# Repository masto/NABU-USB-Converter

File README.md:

# NABU-USB-Converter

Adapter to use a USB keyboard with the NABU PC

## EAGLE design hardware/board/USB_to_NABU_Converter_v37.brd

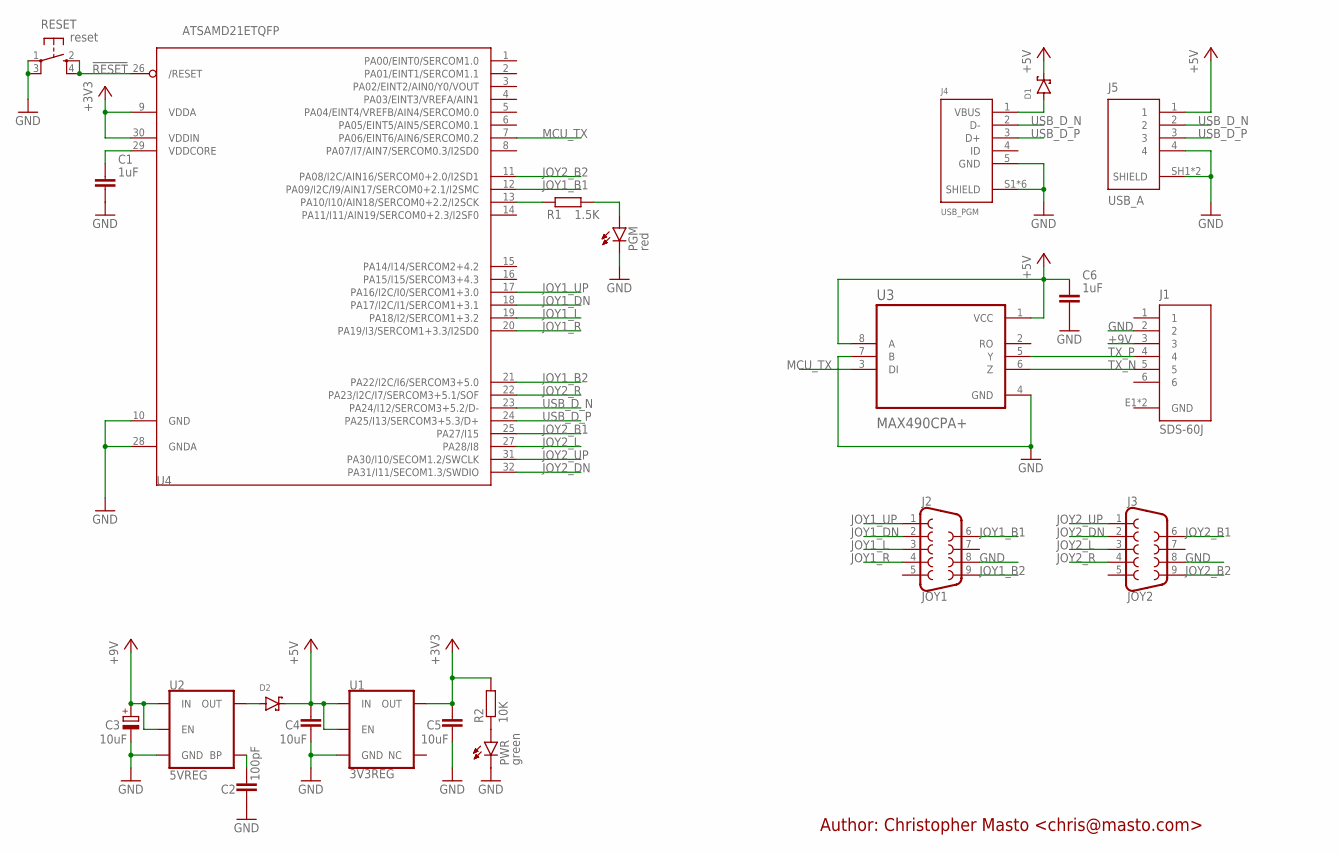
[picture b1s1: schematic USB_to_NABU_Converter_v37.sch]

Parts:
C1, C6: 1uF; CAPC1608X85
C2: 100pF; CAPC1608X85
C3: 10uF; UD-6,3X5,8_NICHICON
C4, C5: 10uF; CAPC1608X85
D1, D2: MBR0520LT1G; SODFL3718X115
J1: SDS-60J; CUI_SDS-60J
J2: JOY1; DB9_MALE
J3: JOY2; DB9_MALE
J4: USB_PGM; AMPHENOL_10118194-0001LF
J5: USB_A; 292303-1
PGM: red; CHIP-LED0603
PWR: green; CHIP-LED0603
R1: 1.5K; R0603
R2: 10K; R0603
RESET: reset; KMR2
U1: 3V3REG; SOT23-5
U2: 5VREG; SOT23-5
U3: MAX490CPA+; DIP794W47P254L991H457Q8
U4: ATSAMD21ETQFP; QFP80P900X900X120-32

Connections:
!RESET: RESET.2 (S), RESET.4 (S1), U4.26 (/RESET)
+3V3: C5.1, R2.2, U1.5 (OUT), U4.9 (VDDA), U4.30 (VDDIN)
+5V: C4.1, C6.1, D1.1 (C), D2.1 (C), J5.1, U1.1 (IN), U1.3 (EN), U3.1 (VCC), U3.8 (A)
+9V: C3.+, J1.3, U2.1 (IN), U2.3 (EN)
GND: C1.2, C2.2, C3.-, C4.2, C5.2, C6.2, J1.2, J1.E1 (GND), J1.E2 (GND), J2.8, J3.8, J4.5 (GND), J4.S1 (SHIELD), J4.S2 (SHIELD), J4.S3 (SHIELD), J4.S4 (SHIELD), J4.S5 (SHIELD), J4.S6 (SHIELD), J5.4, J5.SH1 (SHIELD), J5.SH2 (SHIELD), PGM.C, PWR.C, RESET.1, RESET.3 (P1), U1.2 (GND), U2.2 (GND), U3.4 (GND), U3.7 (B), U4.10 (GND), U4.28 (GNDA)
JOY1_B1: J2.6, U4.12 (PA09/I2C/I9/AIN17/SERCOM0+2.1/I2SMC)
JOY1_B2: J2.9, U4.21 (PA22/I2C/I6/SERCOM3+5.0)
JOY1_DN: J2.2, U4.18 (PA17/I2C/I1/SERCOM1+3.1)
JOY1_L: J2.3, U4.19 (PA18/I2/SERCOM1+3.2)
JOY1_R: J2.4, U4.20 (PA19/I3/SERCOM1+3.3/I2SD0)
JOY1_UP: J2.1, U4.17 (PA16/I2C/I0/SERCOM1+3.0)
JOY2_B1: J3.6, U4.25 (PA27/I15)
JOY2_B2: J3.9, U4.11 (PA08/I2C/AIN16/SERCOM0+2.0/I2SD1)
JOY2_DN: J3.2, U4.32 (PA31/I11/SECOM1.3/SWDIO)
JOY2_L: J3.3, U4.27 (PA28/I8)
JOY2_R: J3.4, U4.22 (PA23/I2C/I7/SERCOM3+5.1/SOF)
JOY2_UP: J3.1, U4.31 (PA30/I10/SECOM1.2/SWCLK)
MCU_TX: U3.3 (DI), U4.7 (PA06/EINT6/AIN6/SERCOM0.2)
unnamed: PWR.A, R2.1
unnamed: C1.1, U4.29 (VDDCORE)
unnamed: R1.1, U4.13 (PA10/I10/AIN18/SERCOM0+2.2/I2SCK)
unnamed: PGM.A, R1.2
unnamed: C2.1, U2.4 (BP)
unnamed: D1.2 (A), J4.1 (VBUS)
unnamed: D2.2 (A), U2.5 (OUT)
TX_N: J1.5, U3.6 (Z)
TX_P: J1.4, U3.5 (Y)
USB_D_N: J4.2 (D-), J5.2, U4.23 (PA24/I12/SERCOM3+5.2/D-)
USB_D_P: J4.3 (D+), J5.3, U4.24 (PA25/I13/SERCOM3+5.3/D+)

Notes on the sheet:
Author: Christopher Masto <chris@masto.com>

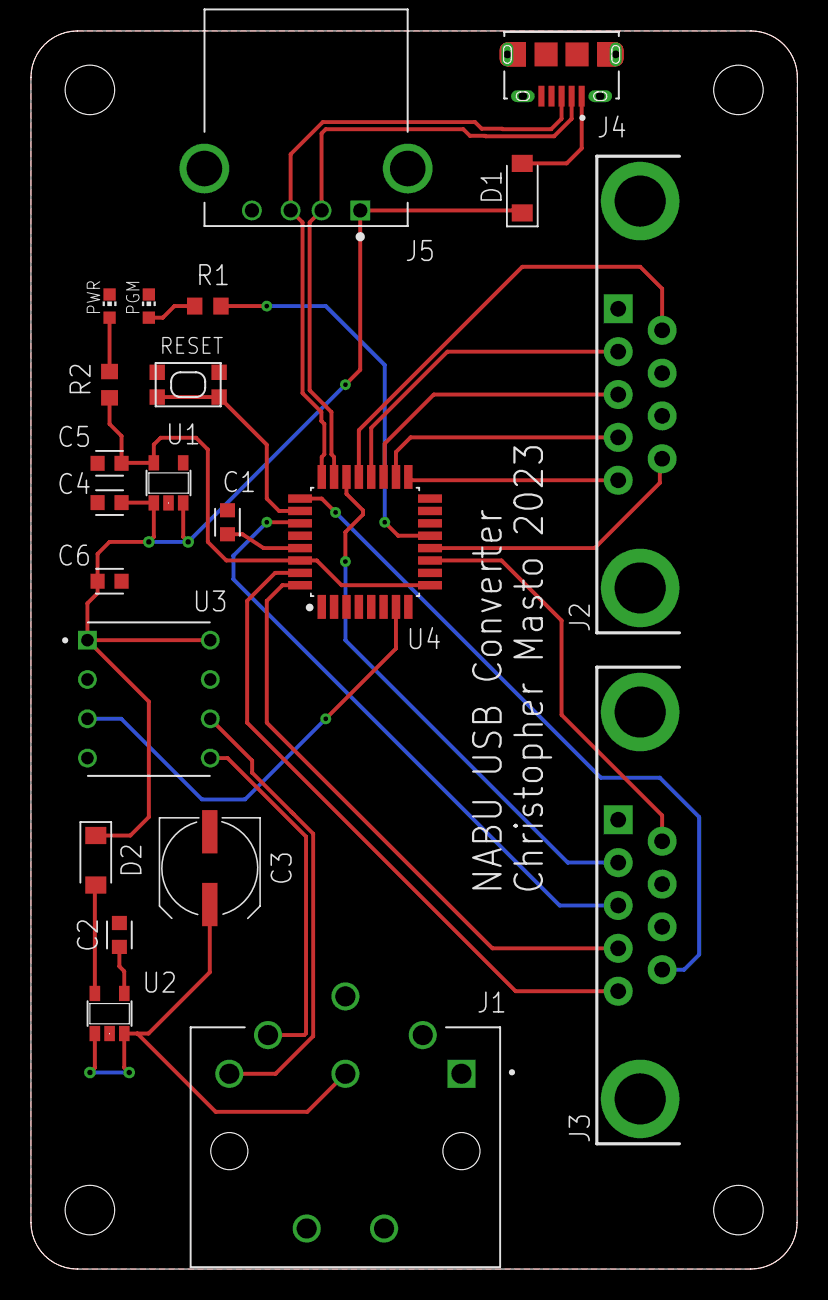
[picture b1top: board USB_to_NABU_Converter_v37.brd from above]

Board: 2 copper layers, 49.5 x 80.0 mm, 22 parts (0 on the bottom side), 29 nets.

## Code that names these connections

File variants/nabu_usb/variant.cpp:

/*
  Copyright (c) 2014-2015 Arduino LLC.  All right reserved.

  This library is free software; you can redistribute it and/or
  modify it under the terms of the GNU Lesser General Public
  License as published by the Free Software Foundation; either
  version 2.1 of the License, or (at your option) any later version.

  This library is distributed in the hope that it will be useful,
  but WITHOUT ANY WARRANTY; without even the implied warranty of
  MERCHANTABILITY or FITNESS FOR A PARTICULAR PURPOSE.
  See the GNU Lesser General Public License for more details.

  You should have received a copy of the GNU Lesser General Public
  License along with this library; if not, write to the Free Software
  Foundation, Inc., 51 Franklin St, Fifth Floor, Boston, MA  02110-1301  USA
*/

#include "variant.h"

/*
 * Pins descriptions
 *
 * Note re: NABU USB Converter
 * My strategy here is to leave as much of the trinket_m0 mapping alone as I
 * can, while adding what's necessary for this board to work.
 * It might have been cleaner to throw it away and start fresh, but I'm hoping
 * to retain some element of backward compatibility and not track down every
 * place that might be relying on these pin indexes.
 */
// JOY2_B2 11 PA08 D0
// JOY1_B1 12 PA09 D6
// JOY1_UP 17 PA16 D12
// JOY1_DN 18 PA17 D23
// JOY1_L 19 PA18 D24
// JOY1_R 20 PA19 D25
// JOY1_B2 21 PA22 D26
// JOY2_R 22 PA23 D27
// JOY2_B1 25 PA27 D28
// JOY2_L 27 PA28 D9
// JOY2_UP 31 PA30 D19
// JOY2_DN 32 PA31 D20
const PinDescription g_APinDescription[] =
    {
        // GPIO 0-4 on external pads
        // D0, ADC, PWM, IRQ, and I2C SDA on sercom2 - no captouch
        {PORTA, 8, PIO_SERCOM_ALT, (PIN_ATTR_DIGITAL | PIN_ATTR_PWM | PIN_ATTR_TIMER), ADC_Channel16, PWM0_CH0, TCC0_CH0, EXTERNAL_INT_NMI}, // TCC0/WO[0]

        // D1, ADC, DAC, IRQ, Captouch and general purpose pin - no timer
        {PORTA, 2, PIO_ANALOG, PIN_ATTR_ANALOG, ADC_Channel0, NOT_ON_PWM, NOT_ON_TIMER, EXTERNAL_INT_2}, // ADC/AIN[0]

        // D2, ADC, PWM, IRQ, and I2C SCL on sercom2 - no captouch
        {PORTA, 9, PIO_SERCOM_ALT, (PIN_ATTR_DIGITAL | PIN_ATTR_PWM | PIN_ATTR_TIMER), ADC_Channel17, PWM0_CH1, TCC0_CH1, EXTERNAL_INT_9}, // TCC0/WO[1]

        // D3, ADC, PWM, IRQ, UART RX, Captouch and general purpose pin
        {PORTA, 7, PIO_SERCOM_ALT, (PIN_ATTR_DIGITAL | PIN_ATTR_PWM | PIN_ATTR_TIMER), ADC_Channel7, PWM1_CH1, TCC1_CH1, EXTERNAL_INT_7}, // TCC1/WO[1]

        // D4, ADC, PWM, IRQ, UART TX, Captouch and general purpose pin
        {PORTA, 6, PIO_SERCOM_ALT, (PIN_ATTR_DIGITAL | PIN_ATTR_PWM | PIN_ATTR_TIMER), ADC_Channel6, PWM1_CH0, TCC1_CH0, EXTERNAL_INT_6}, // TCC1/WO[0]

        // D5, same as D0 but on sercom2 (for SPI sercommin')
        {PORTA, 8, PIO_SERCOM, (PIN_ATTR_DIGITAL | PIN_ATTR_PWM | PIN_ATTR_TIMER), ADC_Channel16, PWM0_CH0, TCC0_CH0, EXTERNAL_INT_NMI}, // TCC0/WO[0]

        // D6, same as D2 but on sercom2 (for SPI sercommin')
        {PORTA, 9, PIO_SERCOM, (PIN_ATTR_DIGITAL | PIN_ATTR_PWM | PIN_ATTR_TIMER), ADC_Channel17, PWM0_CH1, TCC0_CH1, EXTERNAL_INT_9}, // TCC0/WO[1]

        // GPIO 7 & 8 - DotStar internal data/clock
        // ----------------------------------------
        {PORTA, 0, PIO_DIGITAL, 0, ADC_Channel4, NOT_ON_PWM, NOT_ON_TIMER, EXTERNAL_INT_0}, // ADC/AIN[4]
        {PORTA, 1, PIO_DIGITAL, 0, ADC_Channel5, NOT_ON_PWM, NOT_ON_TIMER, EXTERNAL_INT_1}, // ADC/AIN[5]

        // GPIO 9, 10, 11 USB Host enable
        // ----------------------------
        {PORTA, 28, PIO_COM, PIN_ATTR_NONE, No_ADC_Channel, NOT_ON_PWM, NOT_ON_TIMER, EXTERNAL_INT_NONE}, // USB Host enable - GPIO #5
        {PORTA, 24, PIO_COM, PIN_ATTR_NONE, No_ADC_Channel, NOT_ON_PWM, NOT_ON_TIMER, EXTERNAL_INT_NONE}, // USB/DM - GPIO #6
        {PORTA, 25, PIO_COM, PIN_ATTR_NONE, No_ADC_Channel, NOT_ON_PWM, NOT_ON_TIMER, EXTERNAL_INT_NONE}, // USB/DP - GPIO #7

        // GPIO 12 = PA16
        {PORTA, 16, PIO_DIGITAL, (PIN_ATTR_DIGITAL), No_ADC_Channel, NOT_ON_PWM, NOT_ON_TIMER, EXTERNAL_INT_0},

        // GPIO 13 (LED)
        {PORTA, 10, PIO_DIGITAL, (PIN_ATTR_DIGITAL), No_ADC_Channel, NOT_ON_PWM, NOT_ON_TIMER, EXTERNAL_INT_10}, // TX: SERCOM0/PAD[2]

        // Digital 14 - 18, Analog A0-A4
        // A0 same as D1
        {PORTA, 2, PIO_ANALOG, PIN_ATTR_ANALOG, ADC_Channel0, NOT_ON_PWM, NOT_ON_TIMER, EXTERNAL_INT_2},                                                   // ADC/AIN[0]
                                                                                                                                                           // A1, same as D2
        {PORTA, 9, PIO_ANALOG, (PIN_ATTR_ANALOG | PIN_ATTR_DIGITAL | PIN_ATTR_PWM | PIN_ATTR_TIMER), ADC_Channel17, PWM0_CH1, TCC0_CH1, EXTERNAL_INT_9},   // TCC0/WO[1]
                                                                                                                                                           // A2, same as D0
        {PORTA, 8, PIO_ANALOG, (PIN_ATTR_ANALOG | PIN_ATTR_DIGITAL | PIN_ATTR_PWM | PIN_ATTR_TIMER), ADC_Channel16, PWM0_CH0, TCC0_CH0, EXTERNAL_INT_NMI}, // TCC0/WO[0]
                                                                                                                                                           // A3, same as D3
        {PORTA, 7, PIO_ANALOG, (PIN_ATTR_ANALOG | PIN_ATTR_DIGITAL | PIN_ATTR_PWM | PIN_ATTR_TIMER), ADC_Channel7, PWM1_CH1, TCC1_CH1, EXTERNAL_INT_7},    // TCC1/WO[1]
                                                                                                                                                           // A4, same as D4
        {PORTA, 6, PIO_ANALOG, (PIN_ATTR_ANALOG | PIN_ATTR_DIGITAL | PIN_ATTR_PWM | PIN_ATTR_TIMER), ADC_Channel6, PWM1_CH0, TCC1_CH0, EXTERNAL_INT_6},    // TCC1/WO[0]

        // GPIO 19 & 20 (SWCLK & SWDIO)
        // --------------------------
        {PORTA, 30, PIO_SERCOM_ALT, PIN_ATTR_NONE, No_ADC_Channel, NOT_ON_PWM, NOT_ON_TIMER, EXTERNAL_INT_NONE},
        {PORTA, 31, PIO_SERCOM_ALT, PIN_ATTR_NONE, No_ADC_Channel, NOT_ON_PWM, NOT_ON_TIMER, EXTERNAL_INT_NONE},

        // Placeholder #21 & 22 for 'txled' and 'rxled'
        {PORTA, 14, PIO_DIGITAL, (PIN_ATTR_DIGITAL), No_ADC_Channel, NOT_ON_PWM, NOT_ON_TIMER, EXTERNAL_INT_14},
        {PORTA, 15, PIO_DIGITAL, (PIN_ATTR_DIGITAL | PIN_ATTR_PWM | PIN_ATTR_TIMER), No_ADC_Channel, PWM3_CH1, TC3_CH1, EXTERNAL_INT_15},

        // GPIO 23 = PA17, 24 = PA18, 25 = PA19, 26 = PA22, 27 = PA23, 28 = PA27
        {PORTA, 17, PIO_DIGITAL, (PIN_ATTR_DIGITAL), No_ADC_Channel, NOT_ON_PWM, NOT_ON_TIMER, EXTERNAL_INT_1},
        {PORTA, 18, PIO_DIGITAL, (PIN_ATTR_DIGITAL), No_ADC_Channel, NOT_ON_PWM, NOT_ON_TIMER, EXTERNAL_INT_2},
        {PORTA, 19, PIO_DIGITAL, (PIN_ATTR_DIGITAL), No_ADC_Channel, NOT_ON_PWM, NOT_ON_TIMER, EXTERNAL_INT_3},
        {PORTA, 22, PIO_DIGITAL, (PIN_ATTR_DIGITAL), No_ADC_Channel, NOT_ON_PWM, NOT_ON_TIMER, EXTERNAL_INT_6},
        {PORTA, 23, PIO_DIGITAL, (PIN_ATTR_DIGITAL), No_ADC_Channel, NOT_ON_PWM, NOT_ON_TIMER, EXTERNAL_INT_7},
        {PORTA, 27, PIO_DIGITAL, (PIN_ATTR_DIGITAL), No_ADC_Channel, NOT_ON_PWM, NOT_ON_TIMER, EXTERNAL_INT_15},

};

const void *g_apTCInstances[TCC_INST_NUM + TC_INST_NUM] = {TCC0, TCC1, TCC2, TC3, TC4, TC5};

// Multi-serial objects instantiation
SERCOM sercom0(SERCOM0);
SERCOM sercom1(SERCOM1);
SERCOM sercom2(SERCOM2);
SERCOM sercom3(SERCOM3);

Uart Serial1(&sercom0, PIN_SERIAL1_RX, PIN_SERIAL1_TX, PAD_SERIAL1_RX, PAD_SERIAL1_TX);
Uart Serial2(&sercom1, PIN_SERIAL2_RX, PIN_SERIAL2_TX, PAD_SERIAL2_RX, PAD_SERIAL2_TX);

void SERCOM0_Handler()
{
  Serial1.IrqHandler();
}

void SERCOM1_Handler()
{
  Serial2.IrqHandler();
}

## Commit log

2023-05-10 Initialize new PlatformIO project structure
2023-05-10 Add the hacked up demo as a starting point
    This is just a slighly modified version of
    https://github.com/gdsports/usbhostcopro/tree/master/KBDUARTUSBH
    as a proof of concept.
2023-05-10 Create an Arduino variant for our board
    This is initially a straight copy of trinket_m0, and will now be
    modified to enable and rename the I/O pins.
2023-05-11 Reformat
    Since VS Code is going to reformat these files when I save them,
    I am doing a preemptive reformat before committing any actual code
    changes, in order to avoid mixing them. You're welcome.
2023-05-11 Minor change to include guard
2023-05-11 Add remaining pin assignments
    I don't know if they're going to work or not...
2023-05-13 Fix some bad copy/paste
2023-05-13 Add some #defines for the joystick signals
    I'm assuming this will be useful at some point.
2023-05-16 Hack in joystick polling
    Last hack before a total rewrite, but I want to see the joystick
    working.
2023-05-16 Add enclosure models and 3D printing files
2023-05-16 Add electronics design files
2023-05-19 Support alternate serial port for debugging
    This adds the ability to attach a TTL serial interface on JOY2.
    I was going to use this to output debug logs without interfering with
    the NABU interface, but have decided to take a different approach.
    It's still useful to have these pins defined, though. It should have
    no effect if not used.
2023-05-19 Add a README so GitHub stops complaining
    Also, it's a good idea.
2023-05-19 Add some viewable formats of the hardware design
    I've gotten frustrated browsing other people's projects where all they
    have are opaque application-specific files. So maybe don't do that, me.
